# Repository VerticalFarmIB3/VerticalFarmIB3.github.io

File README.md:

Vertical farm - IB3 documentation and webpages

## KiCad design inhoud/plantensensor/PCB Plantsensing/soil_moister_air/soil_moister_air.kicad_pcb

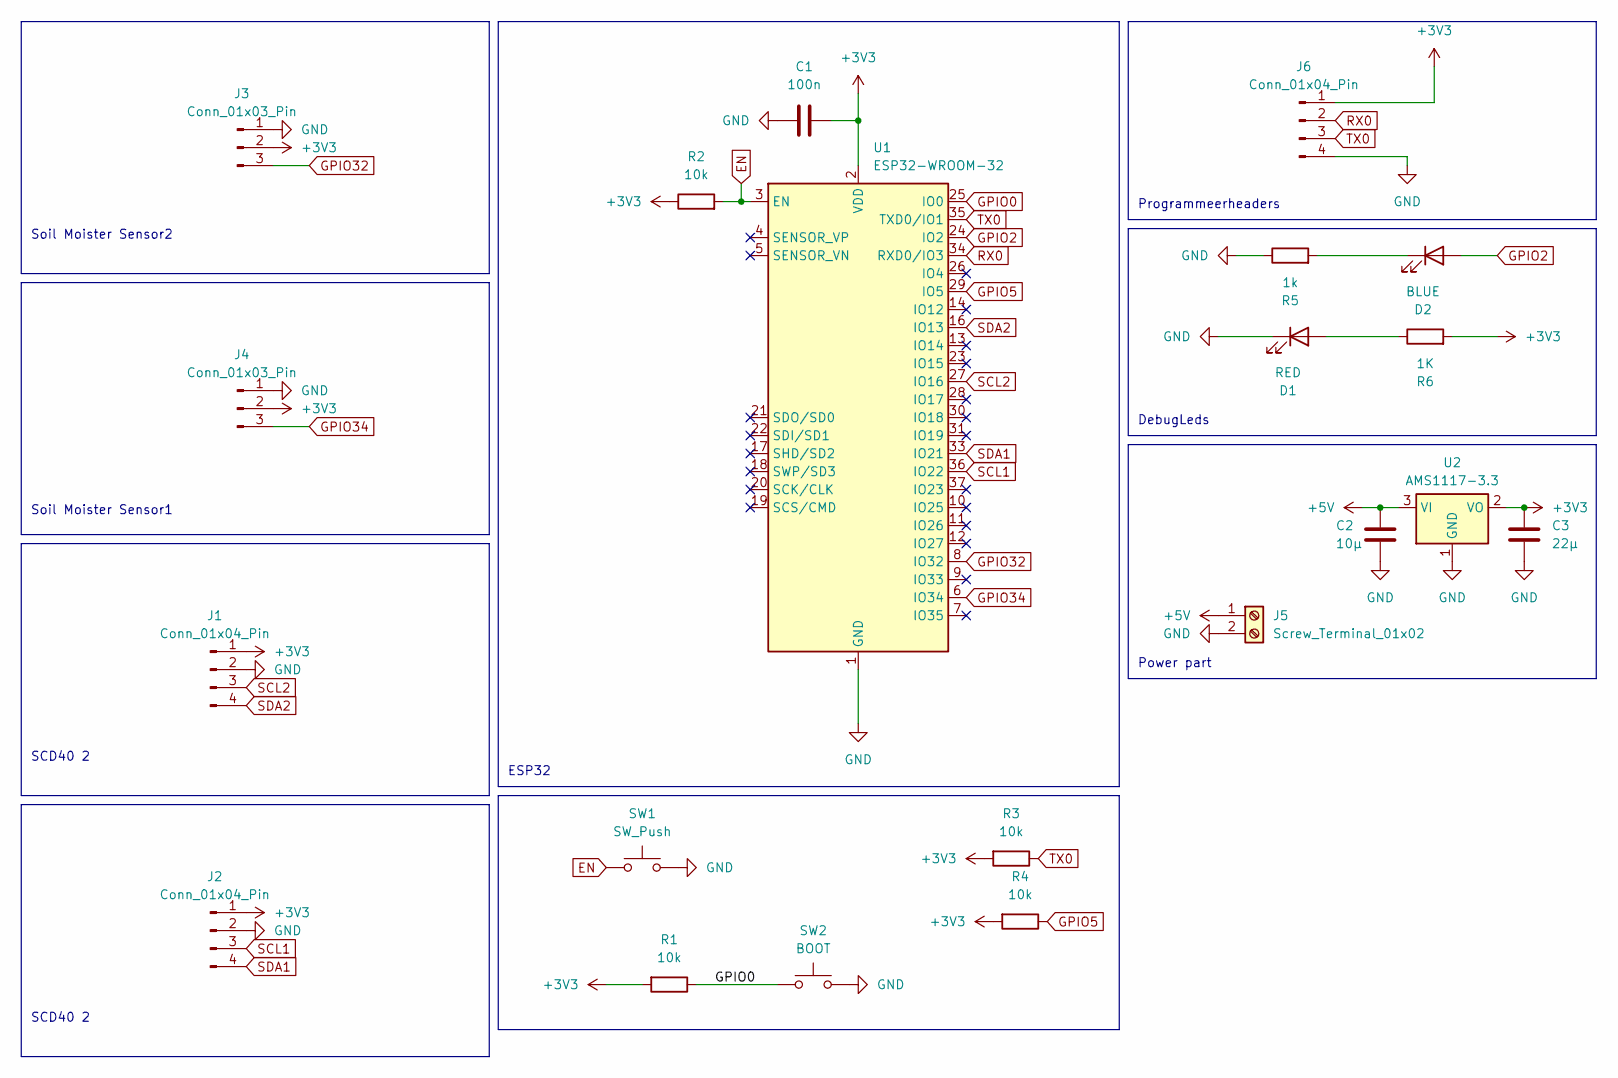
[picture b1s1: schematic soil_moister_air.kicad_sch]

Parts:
C1: 100n; C_0805_2012Metric
C2: 10µ; C_0805_2012Metric
C3: 22µ; C_0805_2012Metric
D1: RED; LED_0805_2012Metric
D2: BLUE; LED_0805_2012Metric
J1, J2, J6: Conn_01x04_Pin; PinHeader_1x04_P2.54mm_Vertical
J3, J4: Conn_01x03_Pin; PinHeader_1x03_P2.54mm_Vertical
J5: Screw_Terminal_01x02; TerminalBlock_bornier-2_P5.08mm
R1, R2, R3, R4: 10k; R_0805_2012Metric
R5: 1k; R_0805_2012Metric
R6: 1K; R_0805_2012Metric
SW1: SW_Push; SW_DIP_SPSTx01_Slide_Copal_CHS-01B_W7.62mm_P1.27mm
SW2: BOOT; SW_DIP_SPSTx01_Slide_Copal_CHS-01B_W7.62mm_P1.27mm
U1: ESP32-WROOM-32
U2: AMS1117-3.3; SOT-223-3_TabPin2

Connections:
+3V3: C1.2, C3.1, J1.1, J2.1, J3.2, J4.2, J6.1, R1.2, R2.1, R3.2, R4.2, R6.2, U1.2 (VDD), U2.2 (VO)
+5V: C2.1, J5.1, U2.3 (VI)
EN: R2.2, SW1.1, U1.3 (EN)
GND: C1.1, C2.2, C3.2, D1.1 (K), J1.2, J2.2, J3.1, J4.1, J5.2, J6.4, R5.1, SW1.2, SW2.2, U1.1 (GND), U1.15 (GND), U1.38 (GND), U1.39 (GND), U2.1 (GND)
GPIO0: R1.1, SW2.1, U1.25 (IO0)
GPIO2: D2.2 (A), U1.24 (IO2)
GPIO5: R4.1, U1.29 (IO5)
GPIO32: J3.3, U1.8 (IO32)
GPIO34: J4.3, U1.6 (IO34)
unnamed: D1.2 (A), R6.1
unnamed: D2.1 (K), R5.2
RX0: J6.2, U1.34 (RXD0/IO3)
SCL1: J2.3, U1.36 (IO22)
SCL2: J1.3, U1.27 (IO16)
SDA1: J2.4, U1.33 (IO21)
SDA2: J1.4, U1.16 (IO13)
TX0: J6.3, R3.1, U1.35 (TXD0/IO1)

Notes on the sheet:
DebugLeds
Soil Moister Sensor1
Soil Moister Sensor2
Programmeerheaders
SCD40 2
ESP32
Power part

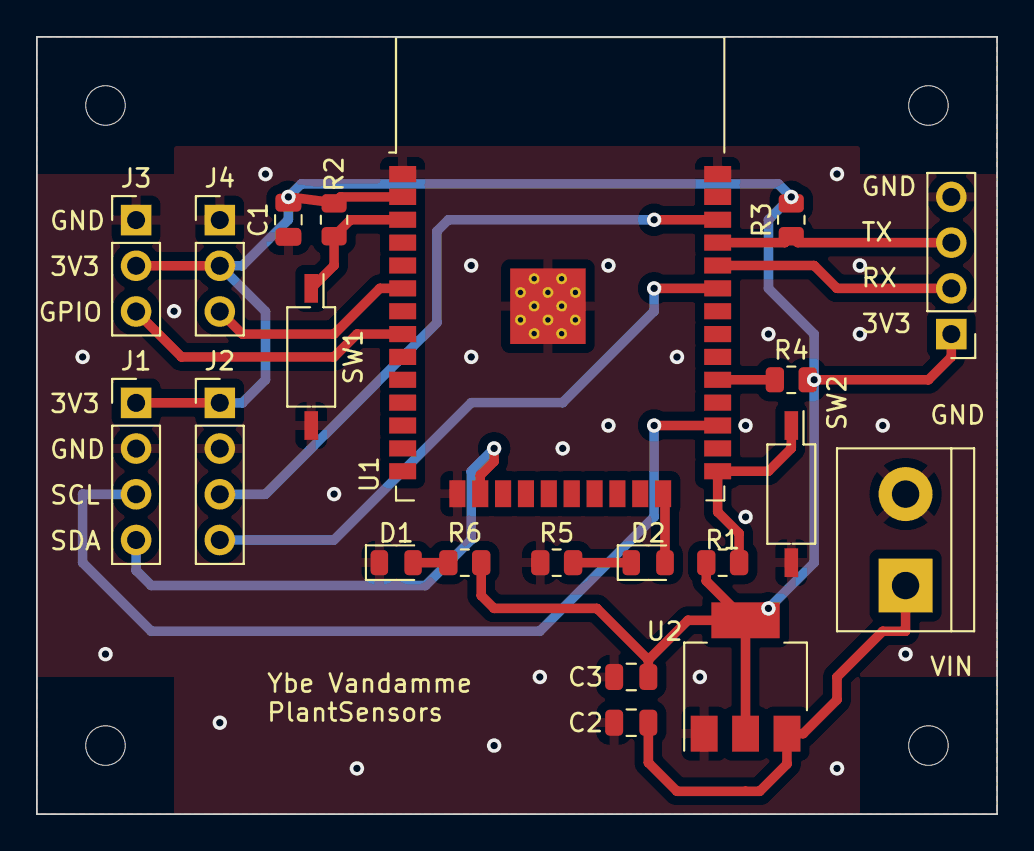
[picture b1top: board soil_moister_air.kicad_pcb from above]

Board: 2 copper layers, 53.3 x 43.2 mm, 21 parts (0 on the bottom side), 17 nets.

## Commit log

2024-05-18 initialise
2024-05-18 initialise logboek
2024-05-18 initialise inhoud logboek
2024-05-18 intialise images
2024-05-18 initialise plantensensor
2024-05-18 intialise
2024-05-18 intiliase aquamonitoring
2024-05-18 intialise aansturing leds
2024-05-18 intialise image
2024-05-18 init leds
2024-05-18 initialise energiemonitoring
2024-05-23 VF IB3 update
2024-05-23 update aqua
2024-05-23 update dashboard
2024-05-23 update engergiemonitoring
2024-05-23 update logboek
2024-05-23 update operation
2024-05-23 update opera
2024-05-24 Revert "delete all to fork"
    This reverts commit 2d5b96d703e90744c07c19ecfc6bb0d3bed4118e.
2024-05-24 update aquamonitoring
2024-05-24 update energiemonitoring
2024-05-24 update leds
2024-05-24 update logbook
2024-05-24 update modularity
2024-05-24 update plantensensor
2024-05-24 update homepage
2024-05-24 make all links point to new github
2024-05-24 Adding last picture
2024-05-24 mistakes modularity
2024-05-24 mistake
